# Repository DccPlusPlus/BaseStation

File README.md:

What’s DCC++
------------

DCC++ is an open-source hardware and software system for the operation of DCC-equipped model railroads.

The system consists of two parts, the DCC++ Base Station and the DCC++ Controller.

The DCC++ Base Station consists of an Arduino micro controller fitted with an Arduino Motor Shield that can be connected directly to the tracks of a model railroad.

The DCC++ Controller provides operators with a customizable GUI to control their model railroad.  It is written in Java using the Processing graphics library and IDE and communicates with the DCC++ Base Station via a standard serial connection over a USB cable or wireless over BlueTooth.

What’s in this Repository
-------------------------

This repository, BaseStation-NodeMCU, contains a stripped-down DCC++ Base Station sketch designed for compiling and uploading into a NodeMCU.  All sketch files are in the folder named DCCpp_NodeMCU. More information about the sketch can be found in the included PDF file.

To utilize this sketch, simply download a zip file of this repository and open the file DCCpp_NodeMCU.ino within the DCCpp_NodeMCU folder using your Arduino IDE.  Please do not rename the folder containing the sketch code, nor add any files to that folder.  The Arduino IDE relies on the structure and name of the folder to properly display and compile the code.

This particular version only supports sensor inputs.

For more information on the overall DCC++ system, please follow the links in the PDF file.

-March 10, 2018

Support for multiple WiFi clients has been added

-April 5, 2018

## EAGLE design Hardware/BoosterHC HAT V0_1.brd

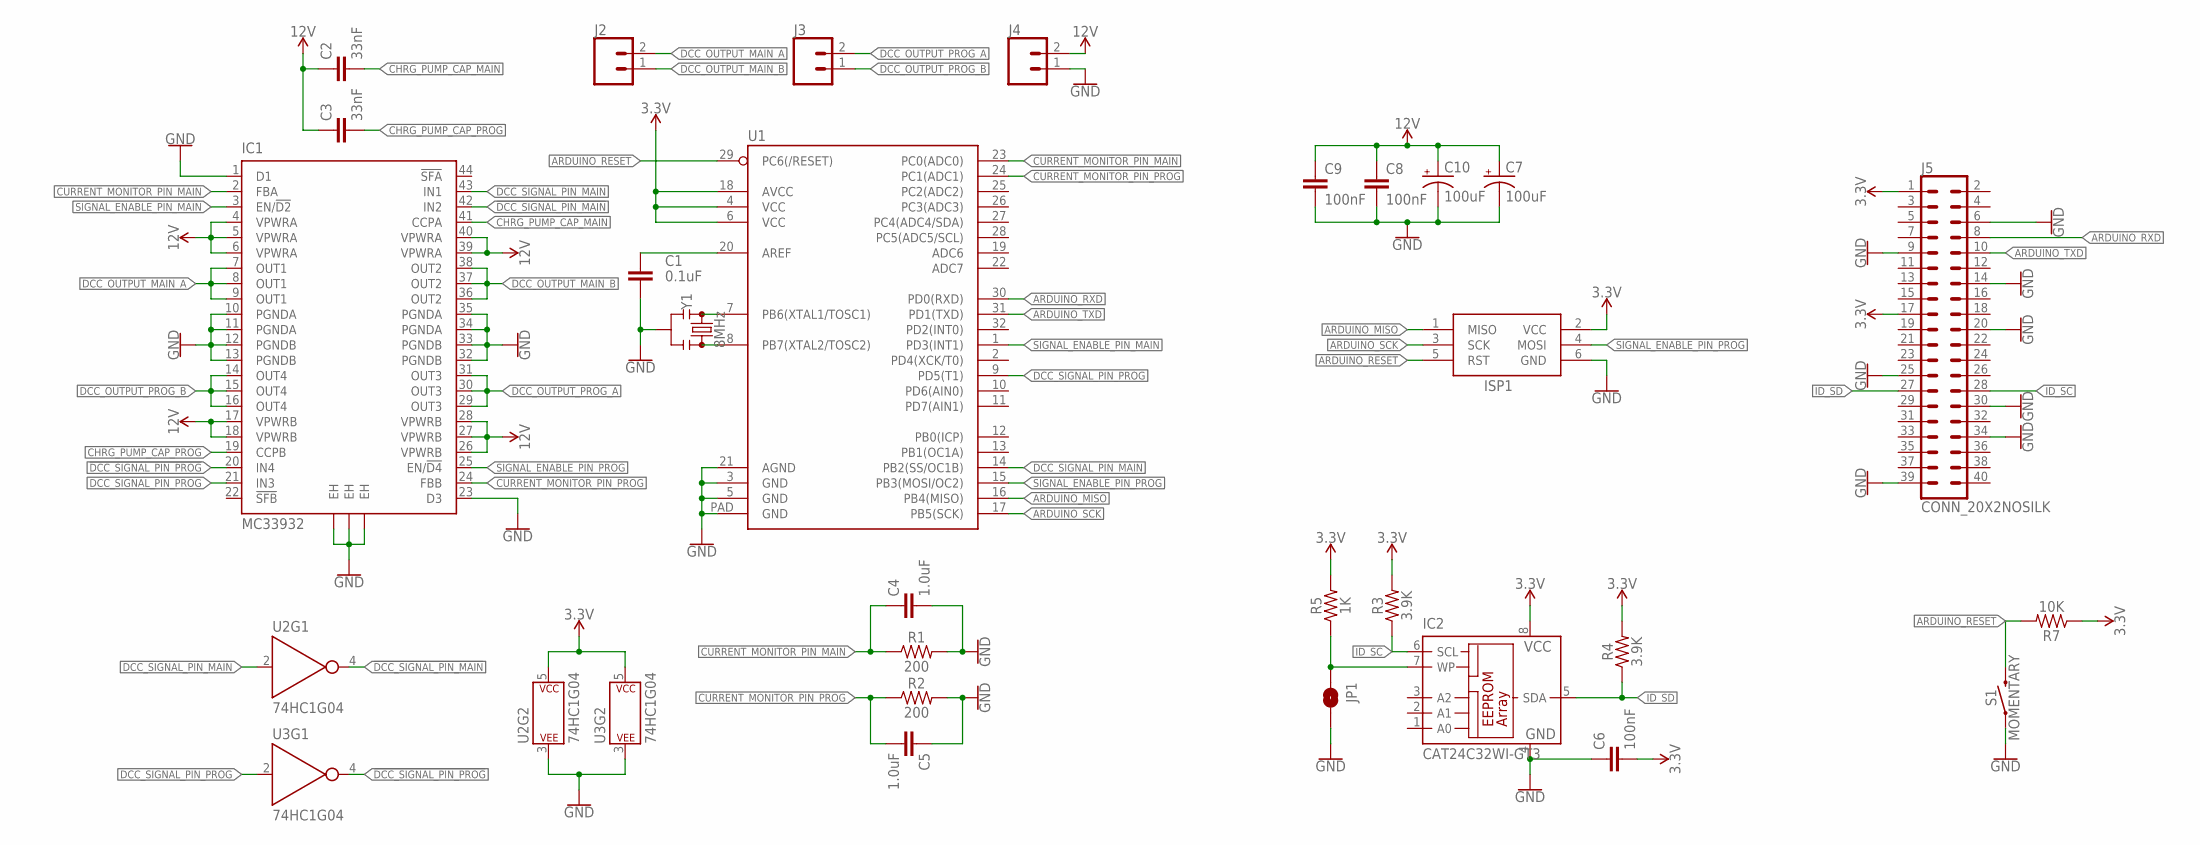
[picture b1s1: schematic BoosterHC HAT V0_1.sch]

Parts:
C1: 0.1uF; 0603
C2, C3: 33nF; 0603
C4, C5: 1.0uF; 0603
C6, C8, C9: 100nF; 0603
C7, C10: 100uF; PANASONIC_D
IC1: MC33932; HSOP44
IC2: CAT24C32WI-GT3; SO-08
ISP1: AVRISP-6; AVRISP
J2, J3, J4: CONN_025MM; SCREWTERMINAL-5MM-2
J5: CONN_20X2NOSILK; 2X20_NOSILK
JP1: JUMPER-SMT_2_NO_SILK; SMT-JUMPER_2_NO_SILK
R1, R2: 200; 0603
R3, R4: 3.9K; 0603
R5: 1K; 0603
R7: 10K; 0603
S1: MOMENTARY; TACTILE_SWITCH_SMD_5.2MM
U1: ATMEGA328P_MLFMLF32; MLF32-PAD
U2, U3: 74HC1G04; SOT353
Y1: 8MHz; RESONATOR-SMD-3.2X1.3

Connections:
3.3V: C6.2, IC2.8 (VCC), ISP1.2 (VCC), J5.1, J5.17, R3.2, R4.2, R5.2, R7.1, U1.4 (VCC), U1.6 (VCC), U1.18 (AVCC), U2.5 (P$V+), U3.5 (P$V+)
12V: C2.1, C3.1, C7.+, C8.1, C9.1, C10.+, IC1.4 (VPWRA), IC1.5 (VPWRA), IC1.6 (VPWRA), IC1.17 (VPWRB), IC1.18 (VPWRB), IC1.26 (VPWRB), IC1.27 (VPWRB), IC1.28 (VPWRB), IC1.39 (VPWRA), IC1.40 (VPWRA), J4.2
!DCC_SIGNAL_PIN_MAIN: IC1.42 (IN2), U2.4 (Y)
!DCC_SIGNAL_PIN_PROG: IC1.20 (IN4), U3.4 (Y)
ARDUINO_MISO: ISP1.1 (MISO), U1.16 (PB4(MISO))
ARDUINO_RESET: ISP1.5 (RST), R7.2, S1.3 (2), S1.4 (2), U1.29 (PC6(/RESET))
ARDUINO_RXD: J5.8, U1.30 (PD0(RXD))
ARDUINO_SCK: ISP1.3 (SCK), U1.17 (PB5(SCK))
ARDUINO_TXD: J5.10, U1.31 (PD1(TXD))
CHRG_PUMP_CAP_MAIN: C2.2, IC1.41 (CCPA)
CHRG_PUMP_CAP_PROG: C3.2, IC1.19 (CCPB)
CURRENT_MONITOR_PIN_MAIN: C4.1, IC1.2 (FBA), R1.1, U1.23 (PC0(ADC0))
CURRENT_MONITOR_PIN_PROG: C5.2, IC1.24 (FBB), R2.1, U1.24 (PC1(ADC1))
DCC_OUTPUT_MAIN_A: IC1.7 (OUT1), IC1.8 (OUT1), IC1.9 (OUT1), J2.2
DCC_OUTPUT_MAIN_B: IC1.36 (OUT2), IC1.37 (OUT2), IC1.38 (OUT2), J2.1
DCC_OUTPUT_PROG_A: IC1.29 (OUT3), IC1.30 (OUT3), IC1.31 (OUT3), J3.2
DCC_OUTPUT_PROG_B: IC1.14 (OUT4), IC1.15 (OUT4), IC1.16 (OUT4), J3.1
DCC_SIGNAL_PIN_MAIN: IC1.43 (IN1), U1.14 (PB2(SS/OC1B)), U2.2 (A)
DCC_SIGNAL_PIN_PROG: IC1.21 (IN3), U1.9 (PD5(T1)), U3.2 (A)
GND: C1.2, C4.2, C5.1, C6.1, C7.-, C8.2, C9.2, C10.-, IC1.1 (D1), IC1.10 (PGNDA), IC1.11 (PGNDA), IC1.12 (PGNDB), IC1.13 (PGNDB), IC1.23 (D3), IC1.32 (PGNDB), IC1.33 (PGNDB), IC1.34 (PGNDA), IC1.35 (PGNDA), IC1.EH@1 (EH), IC1.EH@2 (EH), IC1.EH@3 (EH), IC2.4 (GND), ISP1.6 (GND), J4.1, J5.6, J5.9, J5.14, J5.20, J5.25, J5.30, J5.34, J5.39, JP1.2, R1.2, R2.2, S1.1, S1.2 (1), U1.3 (GND), U1.5 (GND), U1.21 (AGND), U1.PAD (GND), U2.3 (P$V-), U3.3 (P$V-), Y1.2
ID_SC: IC2.6 (SCL), J5.28, R3.1
ID_SD: IC2.5 (SDA), J5.27, R4.1
unnamed: IC2.7 (WP), JP1.1, R5.1
unnamed: U1.8 (PB7(XTAL2/TOSC2)), Y1.3
unnamed: U1.7 (PB6(XTAL1/TOSC1)), Y1.1
unnamed: C1.1, U1.20 (AREF)
SIGNAL_ENABLE_PIN_MAIN: IC1.3 (EN/!D2), U1.1 (PD3(INT1))
SIGNAL_ENABLE_PIN_PROG: IC1.25 (EN/!D4), ISP1.4 (MOSI), U1.15 (PB3(MOSI/OC2))

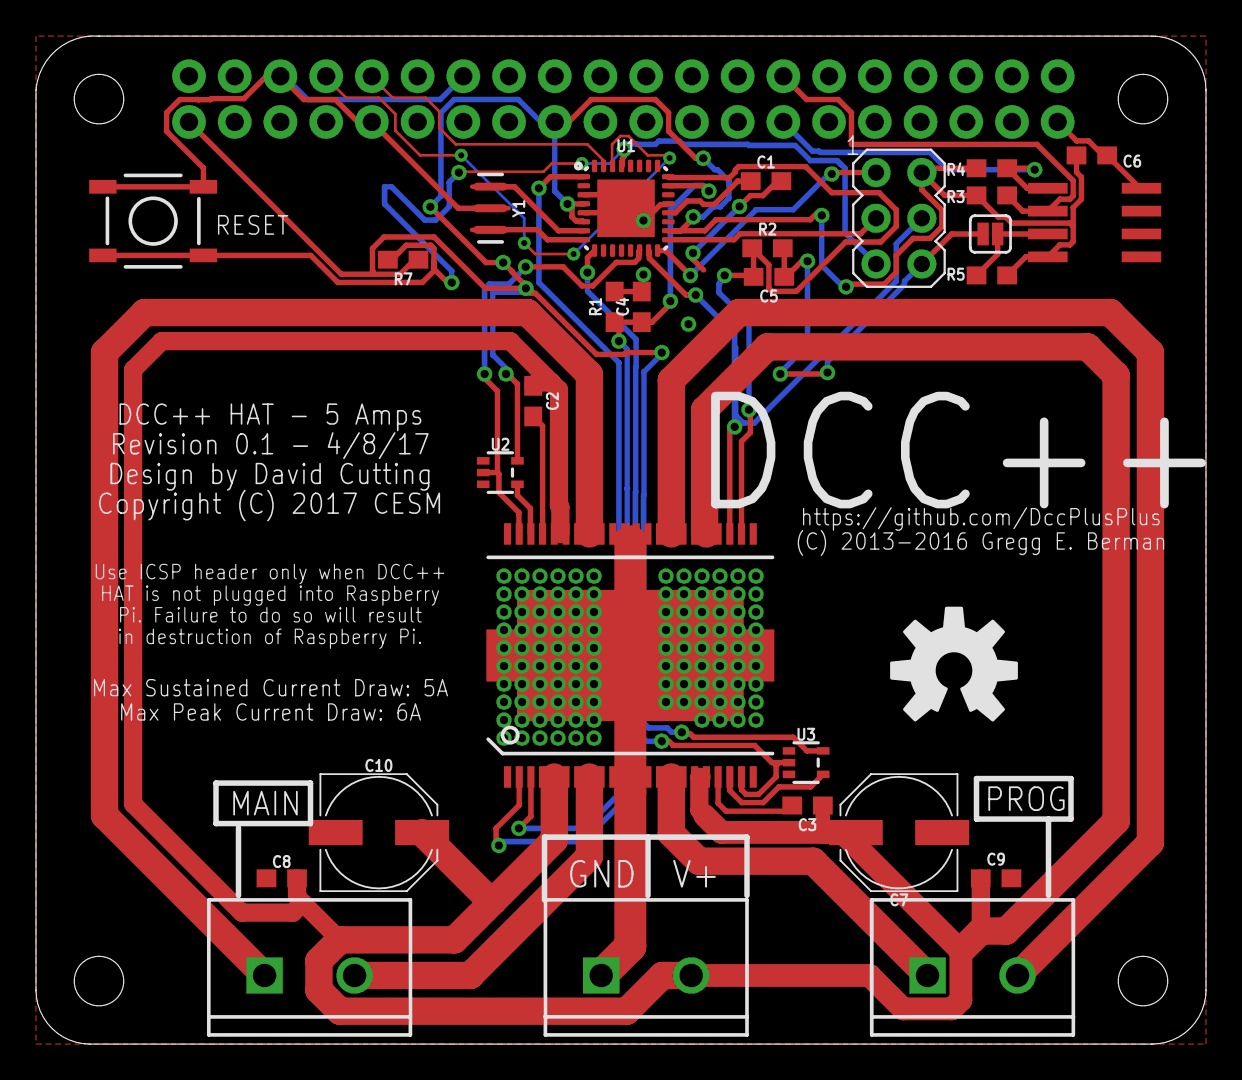
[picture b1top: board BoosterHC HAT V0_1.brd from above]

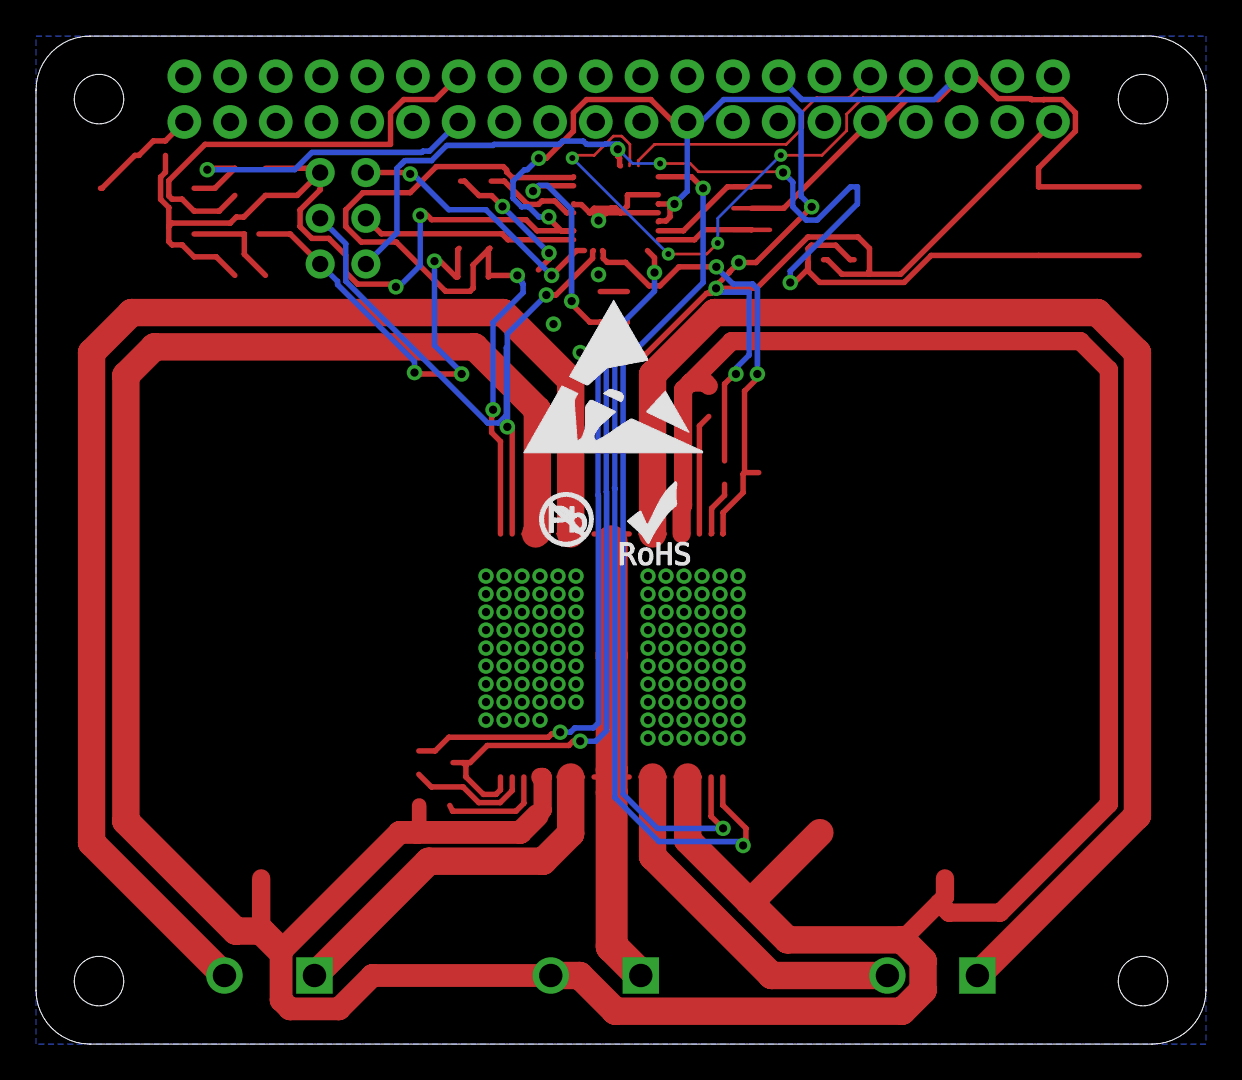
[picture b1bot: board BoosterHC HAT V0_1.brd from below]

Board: 2 copper layers, 65.0 x 56.0 mm, 33 parts (3 on the bottom side), 28 nets.

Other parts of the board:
U$1: OSHW-LOGO-L
U$2: ROHS_LOGO_0.18_IN
U$3: NO_PB_LOGO_0.120
U$4: ESD_10.00

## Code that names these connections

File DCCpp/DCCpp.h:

/**********************************************************************

DCCpp.h
COPYRIGHT (c) 2013-2016 Gregg E. Berman

Part of DCC++ BASE STATION for the Arduino

**********************************************************************/

#include "Config.h"

#ifndef DCCpp_Uno_h
#define DCCpp_Uno_h

/////////////////////////////////////////////////////////////////////////////////////
// RELEASE VERSION
/////////////////////////////////////////////////////////////////////////////////////

#define VERSION "1.2.1+"

/////////////////////////////////////////////////////////////////////////////////////
// AUTO-SELECT ARDUINO BOARD
/////////////////////////////////////////////////////////////////////////////////////

#ifdef ARDUINO_AVR_MEGA                   // is using Mega 1280, define as Mega 2560 (pinouts and functionality are identical)
  #define ARDUINO_AVR_MEGA2560
#endif

#if defined  ARDUINO_AVR_UNO

  #define ARDUINO_TYPE    "UNO"

  #define DCC_SIGNAL_PIN_MAIN 10          // Ardunio Uno  - uses OC1B
  #define DCC_SIGNAL_PIN_PROG 5           // Arduino Uno  - uses OC0B

  #if COMM_INTERFACE != 0                 // Serial was not selected

    #error CANNOT COMPILE - DCC++ FOR THE UNO CAN ONLY USE SERIAL COMMUNICATION - PLEASE SELECT THIS IN THE CONFIG FILE

  #endif

#elif defined  ARDUINO_AVR_MEGA2560

  #define ARDUINO_TYPE    "MEGA"

  #define DCC_SIGNAL_PIN_MAIN 12          // Arduino Mega - uses OC1B
  #define DCC_SIGNAL_PIN_PROG 2           // Arduino Mega - uses OC3B

#else

  #error CANNOT COMPILE - DCC++ ONLY WORKS WITH AN ARDUINO UNO OR AN ARDUINO MEGA 1280/2560

#endif

/////////////////////////////////////////////////////////////////////////////////////
// SELECT MOTOR SHIELD
/////////////////////////////////////////////////////////////////////////////////////

#if MOTOR_SHIELD_TYPE == 0

  #define MOTOR_SHIELD_NAME "ARDUINO MOTOR SHIELD"

  #define SIGNAL_ENABLE_PIN_MAIN 3
  #define SIGNAL_ENABLE_PIN_PROG 11

  #define CURRENT_MONITOR_PIN_MAIN A0
  #define CURRENT_MONITOR_PIN_PROG A1

  #define DIRECTION_MOTOR_CHANNEL_PIN_A 12
  #define DIRECTION_MOTOR_CHANNEL_PIN_B 13

#elif MOTOR_SHIELD_TYPE == 1

  #define MOTOR_SHIELD_NAME "POLOLU MC33926 MOTOR SHIELD"

  #define SIGNAL_ENABLE_PIN_MAIN 9
  #define SIGNAL_ENABLE_PIN_PROG 11

  #define CURRENT_MONITOR_PIN_MAIN A0
  #define CURRENT_MONITOR_PIN_PROG A1

  #define DIRECTION_MOTOR_CHANNEL_PIN_A 7
  #define DIRECTION_MOTOR_CHANNEL_PIN_B 8

#else

  #error CANNOT COMPILE - PLEASE SELECT A PROPER MOTOR SHIELD TYPE

#endif

/////////////////////////////////////////////////////////////////////////////////////
// SELECT COMMUNICATION INTERACE
/////////////////////////////////////////////////////////////////////////////////////

#if COMM_INTERFACE == 0

  #define COMM_TYPE 0
  #define INTERFACE Serial

#elif (COMM_INTERFACE==1) || (COMM_INTERFACE==2) || (COMM_INTERFACE==3)

  #define COMM_TYPE 1
  #define INTERFACE eServer
  #define SDCARD_CS 4
  
#else

  #error CANNOT COMPILE - Please select a proper value for COMM_INTERFACE in CONFIG.H file

#endif

/////////////////////////////////////////////////////////////////////////////////////
// SET WHETHER TO SHOW PACKETS - DIAGNOSTIC MODE ONLY
/////////////////////////////////////////////////////////////////////////////////////

// If SHOW_PACKETS is set to 1, then for select main operations track commands that modify an internal DCC packet register,
// if printFlag for that command is also set to 1, DCC++ BASE STATION will additionally return the 
// DCC packet contents of the modified register in the following format:

//    <* REG: B1 B2 ... Bn CSUM / REPEAT>
//
//    REG: the number of the main operations track packet register that was modified
//    B1: the first hexidecimal byte of the DCC packet
//    B2: the second hexidecimal byte of the DCC packet
//    Bn: the nth hexidecimal byte of the DCC packet
//    CSUM: a checksum byte that is required to be the final byte in any DCC packet
//    REPEAT: the number of times the DCC packet was re-transmitted to the tracks after its iniital transmission
 
#define SHOW_PACKETS  0       // set to zero to disable printing of every packet for select main operations track commands

/////////////////////////////////////////////////////////////////////////////////////

#endif

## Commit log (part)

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2015-10-20 Initial Version
2015-11-16 Added Dynamic Turnout Definition
    Instead of creating Turnouts in the code by defining them in a Turnout
    structure, you now create/edit/delete them dynamically through an
    extension to the <T> command. Also added a <E> command to store
    Turnout settings once specified in the EEPROM for auto loading during
    startup.
2015-11-21 Created EEPROM Storage for Turnouts and Sensors
    Final version that uses new EEStore structure and allows for dynamic
    creation of turnout and sensor definitions.
2015-11-21 Updated comments and documentation for turnouts and sensors
2015-11-22 Added auto-configure for Uno/Mega as well as Motor Shield Type
    * board type detected at compile-time
    * macro to select type of motor shield (Arduino or Pololu MC32926
    * new <e> command that clears EEPROM
    * safety check added to reject throttle command with nReg out-of-bounds
    (<1 or >MaxNumRegs)
2015-11-28 Created Config.h for user settings
2015-11-28 Ethernet - server working
2015-11-29 Added start-up <s> output
2015-11-30 Added <Q> Command for Sensor Status
    <Q> shows the status of all defined sensors by returning a list of <Q
    ID> (sensor active) or <q ID> (sensor inactive)
2015-12-01 Add support for OUTPUT Sensors
    Ok, if it’s an output it’s not really a Sensor, but…
    Allows definition of a Sensor with direction OUTPUT, and adds a Write
    command to change its state.
2015-12-05 Added controllable OUTPUT pins
    Create/edit/delete/control OUTPUT pins for custom use. Pins can be set
    to either ACTIVE or INACTIVE state, where the default behavior is
    ACTIVE=HIGH and INACTIVE=LOW. This default behavior can reversed on
    a pin-by-pin basis. STATE of pin is retained in EEPROM and default
    behavior is to restore upon power-up. This behavior can be changed on
    a pin-by-pin basis to always set STATE to ACTIVE or INACTIVE upon
2015-12-06 Fix to allow for compiling under Mega 1280
    Except for memory, the Mega 1280 and Mega 2560 are identical.
2015-12-12 Added check to ensure UNO is always set to Serial
    Compiler will now throw an error if serial communication is NOT
    selected under an UNO build.
2015-12-12 Documentation correction
2015-12-13 Bug fix in error return of CV read
    Fixed <R> command that reads a CV so that it now returns (-1) upon
    verification error instead of (255). Problem was return value declared
    as byte, not integer in this specific part of the code (in which case a
    (-1 )is incorrectly interpreted as a 255).
2015-12-17 Fixed bug in signal programming track signal generation for Mega
    Typos in setting parameters for OC3B (forgot to change TCCR1B to TCCR3B
    when copying code from the OC1B logic!)
2015-12-20 Added support for Arduino Ethernet-2 Shield
2015-12-20 Re-order setup() so EEPROM loads before Ethernet (if applicable)
    Since the Ethernet Shield can take some tim to initialize, we don’t
    want to wait for that to occur until loaded the EEPROM. By loading
    EEPROM first, pre-defined <Z> outputs will be set immediately, rather
    than after the Ethernet initializes. This is only applicable when
    using Ethernet communications, not Serial (which initializes
    immediately).
2015-12-20 Fixed bug in short-circuit detection for MEGA
    The short-circuit code polled the track current every 10
    “milliseconds.” But Arduino millis() is based on TIMER-0 settings
    which are changed in DCC++ Base Station. The actual polling was closer
    to every 1 millisecond. When Base Station for the Mega for updated to
    utilize TIMER-3 instead of TIMER-0, the millis() function now really
    did count milliseconds, and 10 milliseconds between each track-current
2015-12-21 Added EEPROM storage for RGB Light Color
    RGB Light Control is now complete — next step is convert to optional
    library
2015-12-22 Added store() to RGBLight as part of EEStore::store()
    This change recomputes the storage location for RGB data when an <E>
    command is issued to store sensor, turnout, and output definitions. It
    also writes the current RGB color to EEPROM, even if it has not been
    previously written.
2015-12-24 Add AutoTimer Library
2015-12-24 Implement AutoTimer library and utilize with RGB Light
    Adds AutoTimer library using OCRA of Timer 4. TBD: SEE IF WE CAN MOVE
    THIS TO TIMER 2 AND SCALE COUNTDOWN SO THAT DEFAULT SETTING OF TIMER 2
    DO NOT NEED TO BE CHANGED
2015-12-25 Removed AutoTimer library files and folders
    No longer needed
2015-12-25 Updated RGB to reflect proper wiring of pins
    Green=pin 44, Red=pin 45, Blue=pin 46
2015-12-26 Added descriptions of RGB and EggTimer to the initial comment section
2015-12-27 AutoPilot Initial Confirming Testing
    Must add in EEPROM saving and any logic to enable/disable autopilot
    from DCC++ Controller
2015-12-27 Updated AutoPilot to include EEPROM saving and auto-disable
2015-12-27 Polished up AutoPilot
    Tested interaction between AutoPilot and Controller. Once AutoPilot
    has started (e.g. cab lights are being cycled), starting up Controller
    results in AutoPilot light showing “SINGLE_CAB_RUN.” Turning off
    AutoPilot from Controller stops program and HALTS currently running
    train. Input button and AutoPilot is then disabled for remained of
    session.
2016-01-03 Created <D> diagnostic command
    The <D> command increases the pre-scalers for Timer 0 and 1 (Uno) or
    Timer 3 and 1 (Mega) as well as SLOWS DOWN THE SYSTEM CLOCK by a factor
    of 256. The purpose of this is enable a visual inspection of the DCC
    signals by connecting to an eternal LED or the on-board LED attached to
    pin 13. Once a <D> command is issued, Serial Communication will be
    disrupted. This command is only to be used under the Serial protocol.
2016-01-18 Changed default motor shield back to Arduino
    Inadvertently had Pololu as the default motor shield.
2016-01-31 Initial Build of DCC++ Server
    Added Server code - implemented for sensors
2016-01-31 Added DCC Booster Logic
    First pass of Booster Logic using INT0 (UNO) or INT4 (MEGA)
2016-01-31 Revert "Added DCC Booster Logic"
    This reverts commit 4cf7bd630383f0b578114732ddde7bf67ec3be6b.
2016-02-06 Renamed DCCpp_Uno to just DCCpp
    Reflecting the fact that DCC++ works on both the Uno and the Mega
2016-02-07 Created basic DccServer structures
    Added <J> and <J ID> command to set/show server ID [1-120].
    Added to EEPROM storage, with default=1
2016-02-07 Changed WIRE address range from [1-120] to [0-119]
    * DCC++ MASTER = WIRE Address 0
    * DCC++ BOOSTER = WIRE Address 1-119
2016-02-07 more typo fixes
2016-02-07 fix one documentation error, plus typos
2016-02-07 Created RemoteSensor
    Remote sensors configured on DCC++ BOOSTERS can now be read from the
    DCC++ MASTER. Define sensors with unique IDs on BOOSTERS and they will
    be automatically uploaded to MASTER and MASTER will keep track of
    status.
2016-02-07 Initial Build of Remote Output functionality
    Added Remote Output functions and ability to transit <Y> commands from
    DCC++ SERVER to DCC++ MASTER.
2016-02-07 Completed Remote Output code
    Use <Z ID ACTIVE> for both local and remote OUTPUTS. For remote
    OUTPUTS, ID should have already been defined on respective DCC++
    SERVERS.
2016-02-14 Initial add of DccServer::refresh command
    needs to be completed so that per-server requests are made using <G ID>
    command, instead of general call.
2016-02-15 Re-Writing TWI Library - part 1
    successfully created server receiver mode
2016-02-16 Fully Integrated TWI functionality
    No longer using Wire Library - instead, created custom, non-blocking
    interrupt routing that implements Master Transmitter and Slave Receiver.
    Problems with general call address and <G> command needs to be
    explored. Also need to incorporate all potential error modes into
    interrupt routine.
2016-03-06 Implemented circular serial loop successfully
    Round-robin of 3 Arduinos using <#N COMMAND> structure. Next step is
    creating master reader for Serial1. Also need to tidy up Serial1 -
    define BUS macro.
2016-08-19 adding eclipseArduino project file.
2016-08-19 Enhance the CurrentMonitor to only disable one output when the current sense pin goes over the threshold. Re-enable it after it returns to normal.
    Correcting a few warnings in DCCpp_Uno.ino relating to trailing whitespace
    characters and unused var mac_address when COMM_TYPE is set to SERIAL.
2017-01-20 replaced duplicate code by calling already existing method
2017-01-20 removed additional spaced after \ at lineend
2017-01-20 fixed compiler warning string constant to 'char*' by adding const
2017-01-23 fixed comment spacing
2017-01-25 The rest of the WiThrottle / Inglenook changes
2017-01-27 Update Inglenook to keep its own static LCD object. Working version of LCDThrottle
2017-01-31 Update Inglenook to make use of LCD class. Clean up some junk too.
2017-01-31 Update LCDThrottle to make use of LCD class. Add power on/off with long press of Select
2017-02-01 Working copy. Fixed most things, including getting the LCD to work (duh).
2017-02-01 Remove WiThrottle from this branch, which should be LCDThrottle-specific.
2017-02-01 Forgot to add Inglenook
2017-02-07 Add support for power control and turnout control.
    NOTE: Turnout control does not yet work right, in that
    the throttle doesn't show the turnouts. Still debugging that.
    Also, having a static table of turnout addresses compiled into
    the code seems a bit of a hack.
    Cleaned up some comments etc. as well.
    Switched to DHCP-assigned address.
2017-02-07 Enabled looking at mainRegs for speed/direction
2017-02-08 1) Created an ersatz "session" by separating the while(client.connected()) and while(client.available()) conditions in the input loop in SerialCommand
    This helps with when to send the welcome message and keeps things a bit more
    clean. Should have no effect on normal Ethernet connections. If it does
    have an adverse effect, we can always put the variant while() constructs
    inside a compiler directive.
    2) Fixed the Track Power control
    3) Fixed the direction control on the throttle.
2017-02-08 Function keys now work properly.
    Also removed the line from printIntroMessage() that was a compile-time error.
2017-02-08 Fix responses to function commands for EngineDriver. Not tested.
2017-02-08 Resolved conflicts and restored files for merged withrottle2 and lcd_throttle
2017-02-09 1) Added code for LCD Throttle support. Disabled in Config.h
    2) Added support for Bonjour/Zeroconf registration. Disabled in Config.h
    WARNING: If using the EthernetBonjour library (which this does), you MUST
    make the changes to the Ethernet library as outlined in this Arduino forum
    thread: http://forum.arduino.cc/index.php?topic=234340.0
    ALSO, you must change line 148 of EthernetBonjour.cpp to call
    this->beginMulti() instead of this->beginMulticast() ... apparently
2017-03-01 Try to get withrottle working with the ESP8266 over serial
2017-04-12 Updated version of software to reflect new changes.
2017-04-21 Changed config file to compile for DCC++ HAT by default
2017-04-21 Added all hardware files
2017-05-15 Added new schematic
2017-05-20 Added new design schematic
2018-03-09 Sensors Only Version for NodeMCU
    Uses a WiFi connection only to talk to JMRI.
2018-03-10 Renamed from Uno to NodeMCU
    Also edited the description in contained within the DCCpp_NodeMCU.ino file.
2018-04-05 Implimented multiple clients on WiFi
2018-04-07 Remote Sensors now supported
    Similar to the way it is implemented in DCC++32
2018-09-15 Remove extra space before newlines after \ characters
2018-09-15 Comment alignment, and fix typos
2020-05-23 Add Support for software serial port

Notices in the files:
Hardware/BoosterHC HAT V0_1.brd:
Copyright (C) 2017 CESM
parts and their libraries:
SparkFun-Capacitors: Licensing: Creative Commons ShareAlike 4.0 International - https://creativecommons.org/licenses/by-sa/4.0
